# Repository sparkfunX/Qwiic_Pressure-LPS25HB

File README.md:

SparkFun Qwiic Pressure with LPS25HB
========================================

[*Qwiic Pressure Sensor - LPS25HB (SPX-14767)*](https://www.sparkfun.com/products/14767)

The LPS25HB is an absolute pressure sensor which means that it has an internal vacuum as a reference. (As opposed to *differential* and *gage* sensors, see [this](https://cdn.sparkfun.com/assets/e/1/2/4/1/HoneywellTechnicalNote_Absolute_v_Gage_pressure.pdf) description by Honeywell for more info) Absolute pressure sensors are often used as altimeters however they can be seen in other applications like the [Robotic Finger Sensor v2](https://www.sparkfun.com/products/14687). 

You can use this absolute pressure sensor to inform a drone autopilot of altitude, make a personal weather station, or maybe even help test someone's lung function! As part of the Qwiic system adding more capabilities like data logging with the [Qwiic OpenLog](https://www.sparkfun.com/products/14641) is a cinch!

The LPS25HB is the newest version of the LPS25H by STMicroelectronics featuring the widest range of sensing pressures (26 kPa to 126 kPa) and very high precision (as low as 1 Pa RMS, which equates to approximately 8 centimeters of air at sea level). Other features such as the 25 Hz update rate and durability to withstand nearly 2.5 MPa over-pressure make this a great choice for absolute pressure sensor. Additionally the LPS25HB comes in a stylish plastic IC package, as opposed to the standard metal casing seen on most other pressure sensors.

In addition to the Qwiic connectors this sensor breakout exposes the I2C and SPI lines as plated through hole (PTH) connections on either side. SPI access will allow for even faster communication with the sensor (up to 10 MHz!) 

This board is one of our many [Qwiic](https://www.sparkfun.com/qwiic) compatible boards! Simply plug and go. No soldering, no figuring out which is SDA or SCL, and no voltage regulation or translation required!

SparkFun labored with love to create this code. Feel like supporting open source hardware? 
Buy a [breakout board](https://www.sparkfun.com/products/14688) from SparkFun!

Repository Contents
-------------------

* **/Documents** - Datasheets
* **/Hardware** - Eagle design files (.brd, .sch)

Library
--------------
* **[Arduino Library](https://github.com/sparkfun/SparkFun_LPS25HB_Arduino_Library)** - Library for reading pressure and changing sensor settings

License Information
-------------------

This product is _**open source**_! 

If you have any questions or concerns on licensing, please contact techsupport@sparkfun.com.

Please use, reuse, and modify these files as you see fit. Please maintain attribution to SparkFun Electronics and release any derivative under the same license.

Distributed as-is; no warranty is given.

- Your friends at SparkFun.

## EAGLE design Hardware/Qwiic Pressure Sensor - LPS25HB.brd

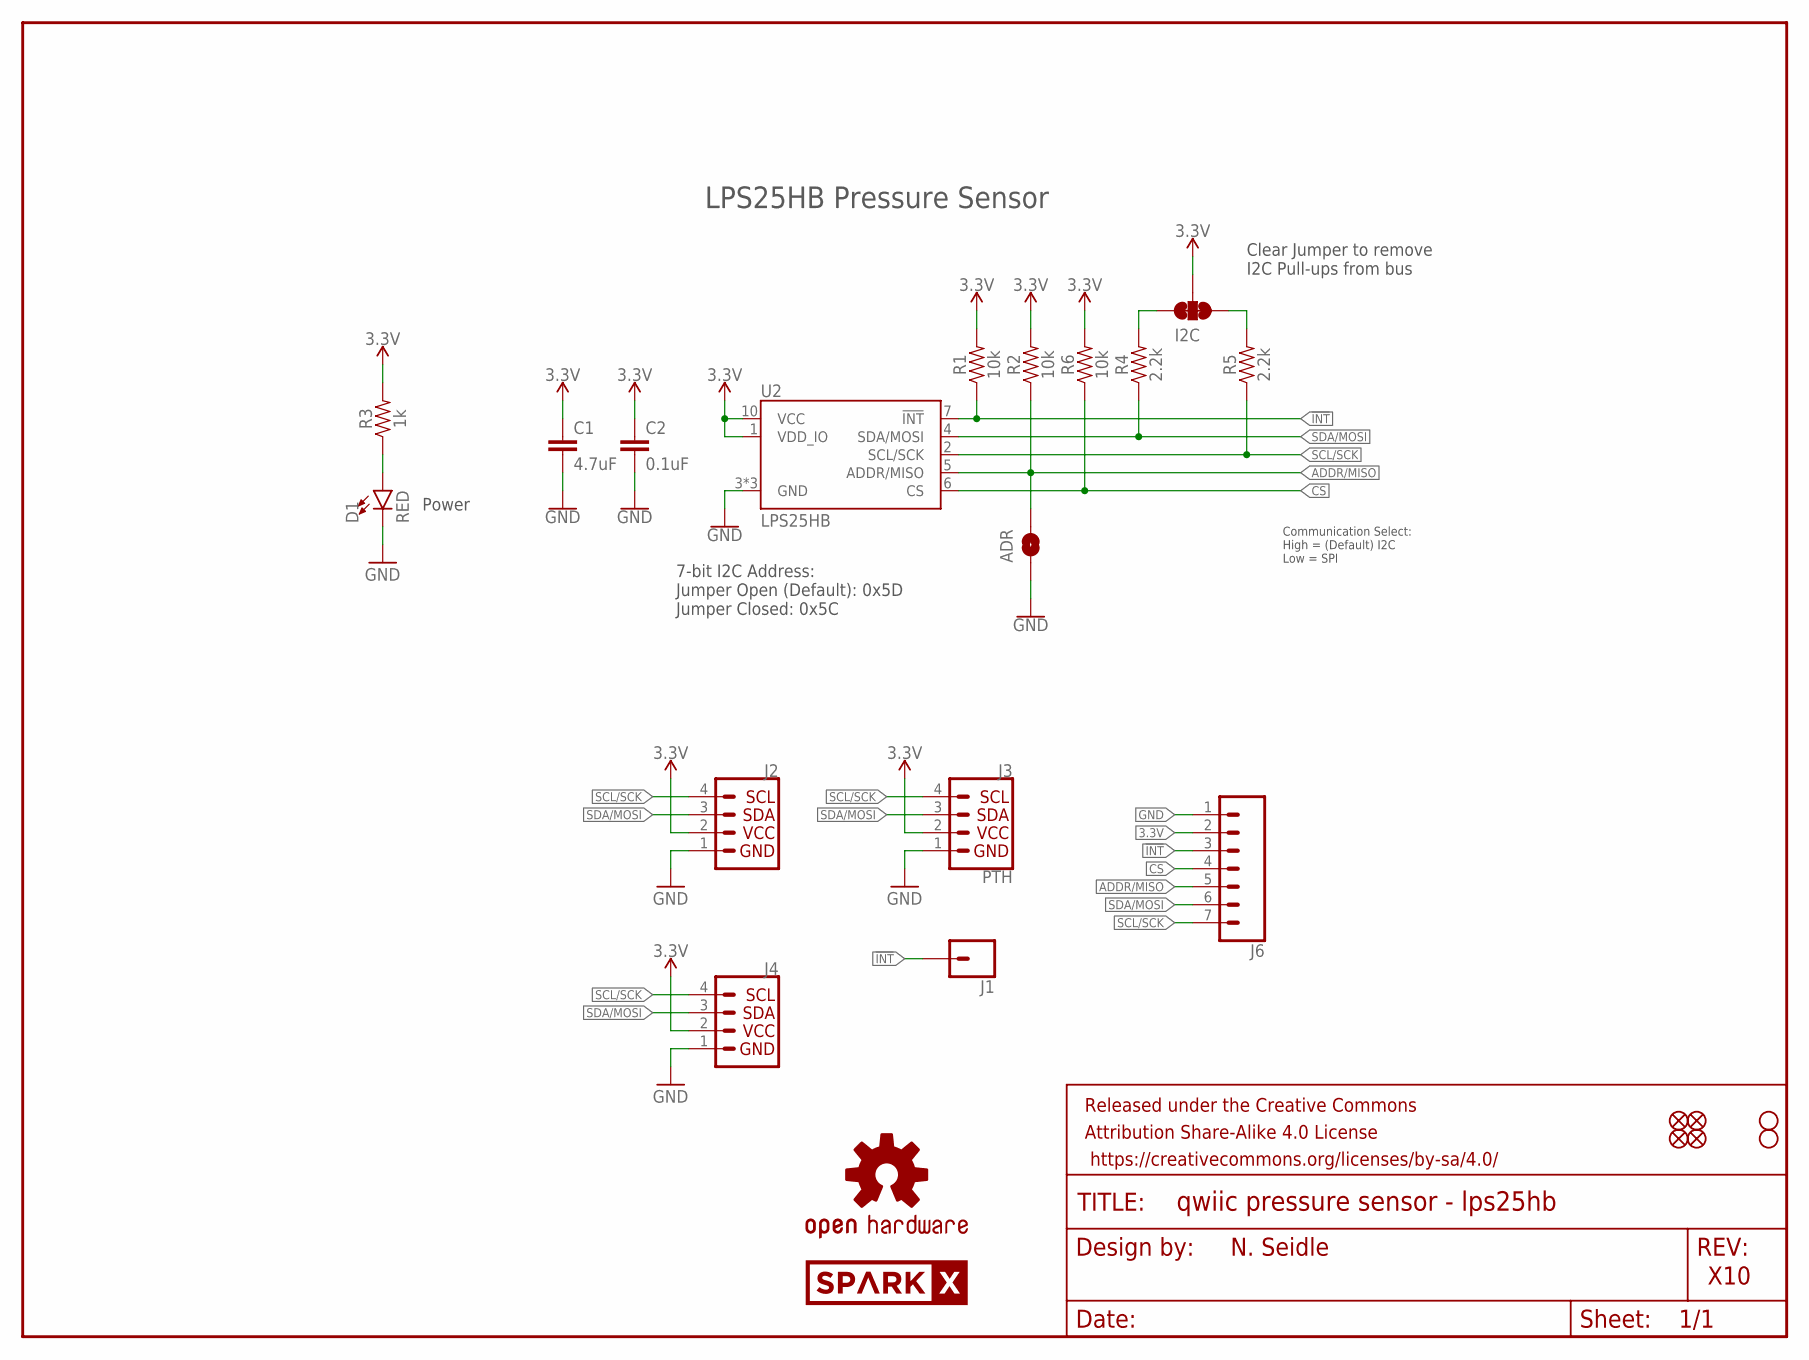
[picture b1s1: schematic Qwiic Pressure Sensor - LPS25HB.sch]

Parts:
ADR: JUMPER-SMT_2_NO_SILK; SMT-JUMPER_2_NO_SILK
C1: 4.7uF; 0603
C2: 0.1uF; 0603
D1: RED; LED-0603
FRAME1: FRAME-LETTER; CREATIVE_COMMONS
I2C: JUMPER-SMT_3_2-NC_TRACE_SILK; SMT-JUMPER_3_2-NC_TRACE_SILK
J1: CONN_01PTH_NO_SILK_YES_STOP; 1X01_NO_SILK
J2, J4: I2C_STANDARDQWIIC; 1X04_1MM_RA
J3: PTH; 1X04_NO_SILK
J6: CONN_07NO_SILK; 1X07_NO_SILK
JP1, JP2, JP5, JP6: FIDUCIALUFIDUCIAL; MICRO-FIDUCIAL
JP3, JP4: STAND-OFF
LOGO1: OSHW-LOGOMINI; OSHW-LOGO-MINI
R1, R2, R6: 10k; 0603
R3: 1k; 0603
R4, R5: 2.2k; 0603
U2: LPS25HB
U$2: SPARKX-LOGO4; SPARKX-MEDIUM

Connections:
3.3V: C1.1, C2.1, I2C.2, J2.2, J3.2 (VCC), J4.2, J6.2, R1.2, R2.2, R3.2, R6.2, U2.1 (VDD_IO), U2.10 (VCC)
!INT: J1.1, J6.3, R1.1, U2.7 (!INT)
ADDR/MISO: ADR.2, J6.5, R2.1, U2.5 (ADDR/MISO)
CS: J6.4, R6.1, U2.6 (CS)
GND: ADR.1, C1.2, C2.2, D1.C, J2.1, J3.1 (GND), J4.1, J6.1, U2.3 (GND), U2.8 (GND), U2.9 (GND)
unnamed: I2C.1, R5.2
unnamed: I2C.3, R4.2
unnamed: D1.A, R3.1
SCL/SCK: J2.4, J3.4 (SCL), J4.4, J6.7, R5.1, U2.2 (SCL/SCK)
SDA/MOSI: J2.3, J3.3 (SDA), J4.3, J6.6, R4.1, U2.4 (SDA/MOSI)

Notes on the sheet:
N. Seidle
X10
Clear Jumper to remove I2C Pull-ups from bus
Power
LPS25HB Pressure Sensor
7-bit I2C Address: Jumper Open (Default): 0x5D Jumper Closed: 0x5C
Communication Select: High = (Default) I2C Low = SPI

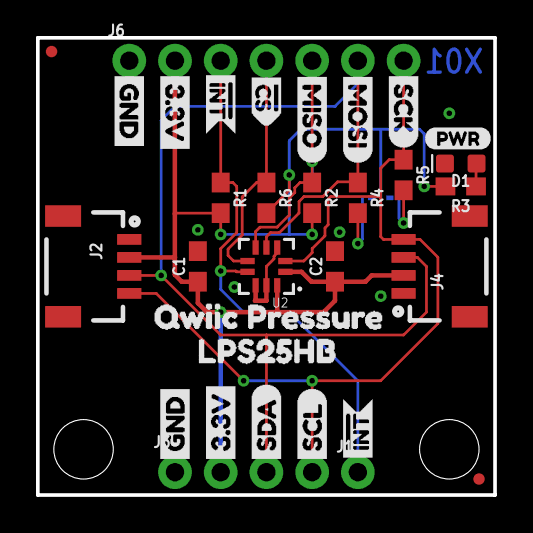
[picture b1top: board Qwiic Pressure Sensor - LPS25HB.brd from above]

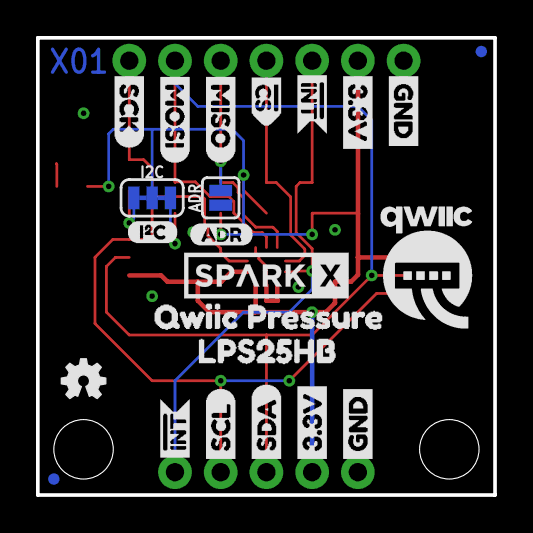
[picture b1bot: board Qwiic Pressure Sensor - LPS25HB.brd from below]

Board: 2 copper layers, 25.4 x 25.4 mm, 58 parts (23 on the bottom side), 10 nets.

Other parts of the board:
U$1, U$37: QWIIC_PRESSURE1
U$3, U$22, U$31, U$32: GND1
U$4, U$21, U$30, U$33: 3#3V2
U$5, U$27: SDA8
U$6, U$26: SCL9
U$7, U$35: LPS25HB0
U$9: QWIIC-LOGO-MEDIUM
U$10, U$11: MISO
U$12: I_SUPER2_C-()-03
U$15: PWR-()-03
U$16, U$17: MOSI
U$18, U$19: SCK-[)
U$20, U$23: CS#-[>
U$24, U$25, U$28, U$29: INT#-[<
U$34: ADR-()-03

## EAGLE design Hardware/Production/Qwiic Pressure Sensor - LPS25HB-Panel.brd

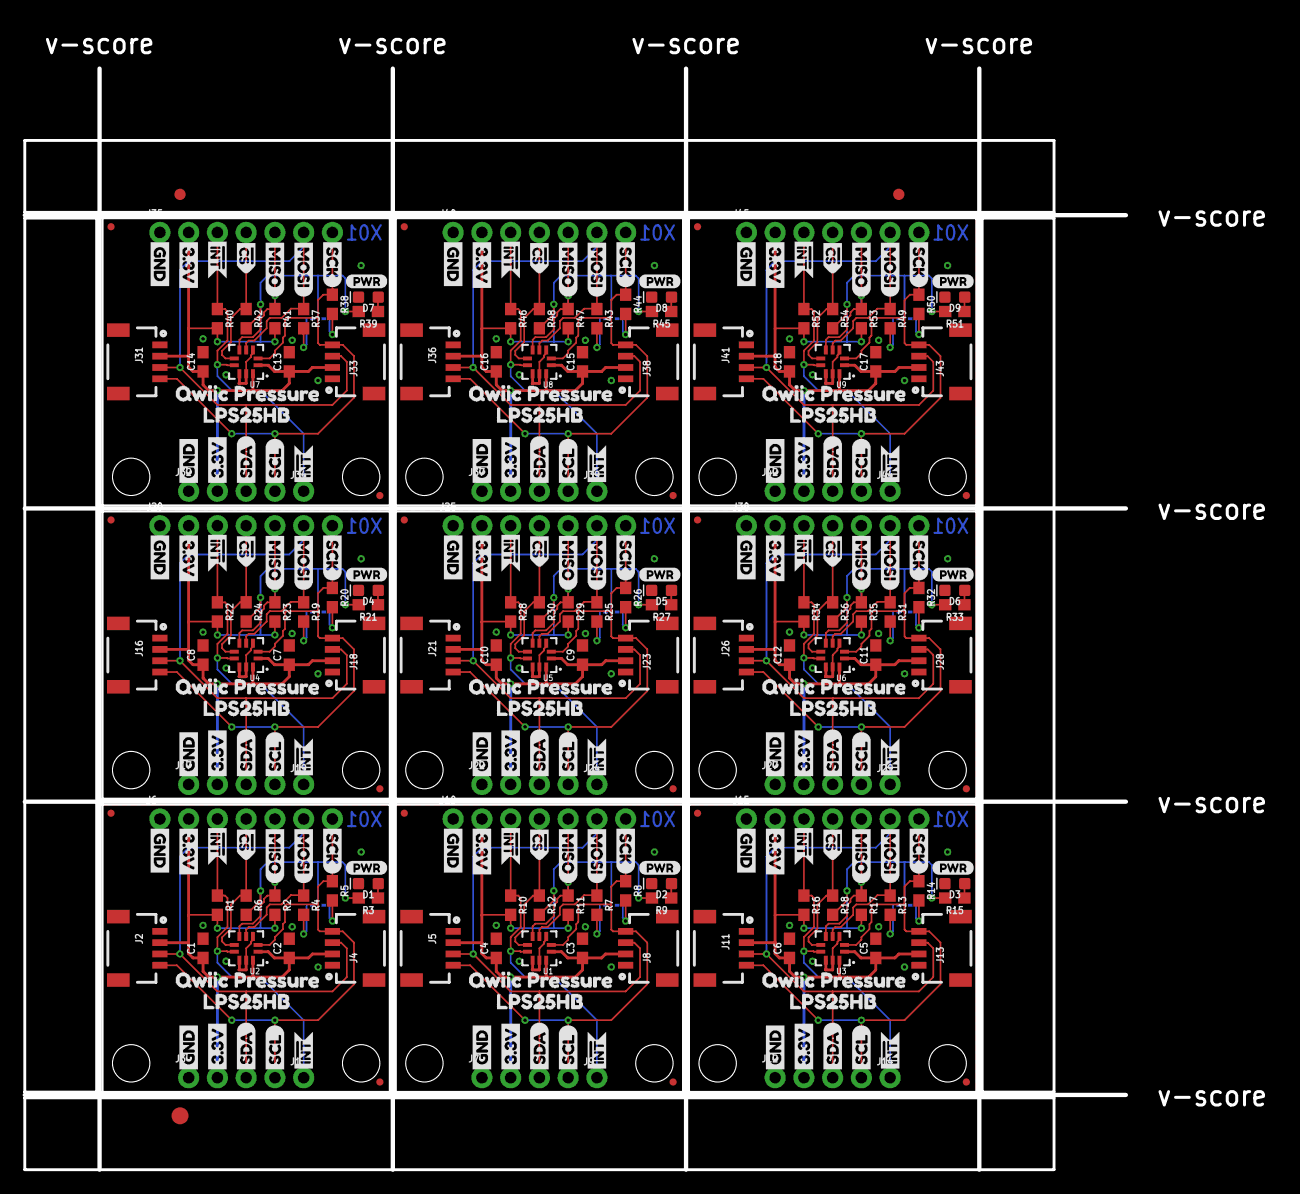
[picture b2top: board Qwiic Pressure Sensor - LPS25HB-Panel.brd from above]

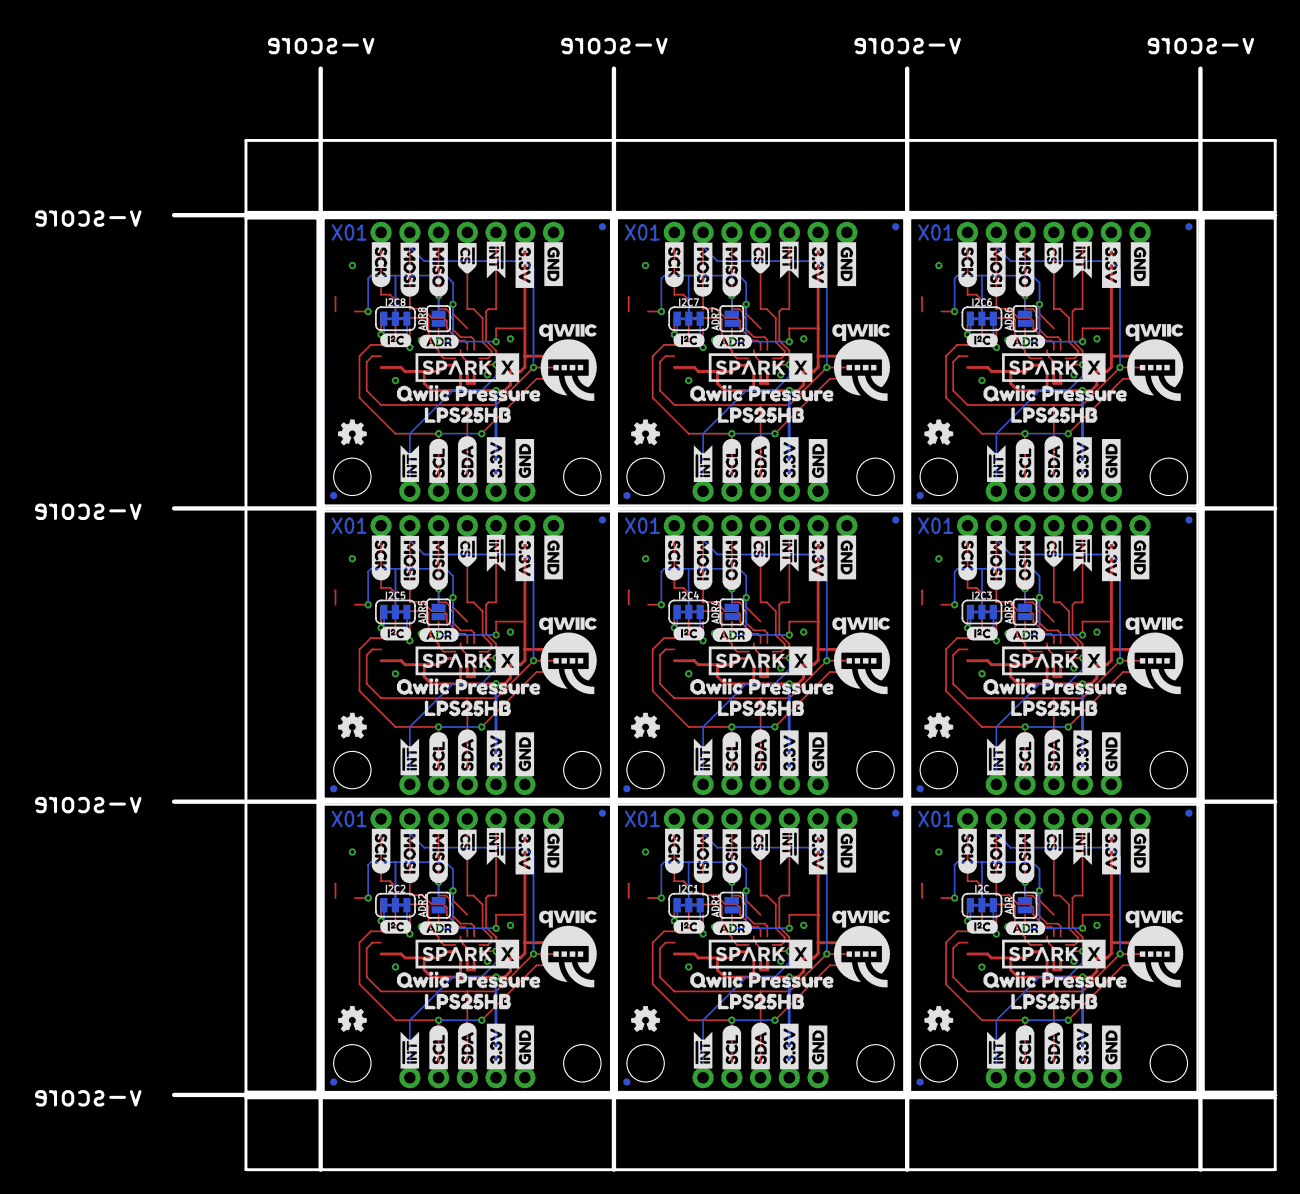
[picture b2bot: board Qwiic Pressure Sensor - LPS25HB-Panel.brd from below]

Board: 2 copper layers, 110.5 x 101.2 mm, 516 parts (207 on the bottom side), 90 nets.

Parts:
ADR, ADR1, ADR2, ADR3, ADR4, ADR5, ADR6, ADR7, ADR8: SMT-JUMPER_2_NO_SILK
C1, C4, C6, C8, C10, C12, C14, C16, C18: 4.7uF; 0603
C2, C3, C5, C7, C9, C11, C13, C15, C17: 0.1uF; 0603
D1, D2, D3, D4, D5, D6, D7, D8, D9: RED; LED-0603
E$1, E$2: FIDUCIAL-1X2
E$3: FIDUCIAL-1.5X3
I2C, I2C1, I2C2, I2C3, I2C4, I2C5, I2C6, I2C7, I2C8: SMT-JUMPER_3_2-NC_TRACE_SILK
J1, J9, J14, J19, J24, J29, J34, J39, J44: 1X01_NO_SILK
J2, J4, J5, J8, J11, J13, J16, J18, J21, J23, J26, J28, J31, J33, J36, J38, J41, J43: 1X04_1MM_RA
J3, J7, J12, J17, J22, J27, J32, J37, J42: PTH; 1X04_NO_SILK
J6, J10, J15, J20, J25, J30, J35, J40, J45: 1X07_NO_SILK
JP1, JP2, JP5, JP6, JP9, JP10, JP11, JP12, JP15, JP16, JP17, JP18, JP21, JP22, JP23, JP24, JP27, JP28, JP29, JP30, JP33, JP34, JP35, JP36, JP39, JP40, JP41, JP42, JP45, JP46, JP47, JP48, JP51, JP52, JP53, JP54: FIDUCIALUFIDUCIAL; MICRO-FIDUCIAL
JP3, JP4, JP7, JP8, JP13, JP14, JP19, JP20, JP25, JP26, JP31, JP32, JP37, JP38, JP43, JP44, JP49, JP50: STAND-OFF
LOGO1, LOGO2, LOGO3, LOGO4, LOGO5, LOGO6, LOGO7, LOGO8, LOGO9: OSHW-LOGOMINI; OSHW-LOGO-MINI
R1, R2, R6, R10, R11, R12, R16, R17, R18, R22, R23, R24, R28, R29, R30, R34, R35, R36, R40, R41, R42, R46, R47, R48, R52, R53, R54: 10k; 0603
R3, R9, R15, R21, R27, R33, R39, R45, R51: 1k; 0603
R4, R5, R7, R8, R13, R14, R19, R20, R25, R26, R31, R32, R37, R38, R43, R44, R49, R50: 2.2k; 0603
U1, U2, U3, U4, U5, U6, U7, U8, U9: LPS25HB
U$1, U$37, U$64, U$65, U$97, U$98, U$130, U$131, U$163, U$164, U$196, U$197, U$229, U$230, U$262, U$263, U$295, U$296: QWIIC_PRESSURE1
U$2, U$8, U$67, U$100, U$133, U$166, U$199, U$232, U$265: SPARKX-LOGO4; SPARKX-MEDIUM
U$3, U$14, U$22, U$31, U$32, U$39, U$59, U$60, U$69, U$72, U$92, U$93, U$102, U$105, U$125, U$126, U$135, U$138, U$158, U$159, U$168, U$171, U$191, U$192, U$201, U$204, U$224, U$225, U$234, U$237, U$257, U$258, U$267, U$270, U$290, U$291: GND1
U$4, U$13, U$21, U$30, U$33, U$40, U$58, U$61, U$68, U$73, U$91, U$94, U$101, U$106, U$124, U$127, U$134, U$139, U$157, U$160, U$167, U$172, U$190, U$193, U$200, U$205, U$223, U$226, U$233, U$238, U$256, U$259, U$266, U$271, U$289, U$292: 3#3V2
U$5, U$27, U$38, U$41, U$71, U$74, U$104, U$107, U$137, U$140, U$170, U$173, U$203, U$206, U$236, U$239, U$269, U$272: SDA8
U$6, U$26, U$36, U$42, U$70, U$75, U$103, U$108, U$136, U$141, U$169, U$174, U$202, U$207, U$235, U$240, U$268, U$273: SCL9
U$7, U$35, U$63, U$66, U$96, U$99, U$129, U$132, U$162, U$165, U$195, U$198, U$228, U$231, U$261, U$264, U$294, U$297: LPS25HB0
U$9, U$43, U$76, U$109, U$142, U$175, U$208, U$241, U$274: QWIIC-LOGO-MEDIUM
U$10, U$11, U$46, U$47, U$79, U$80, U$112, U$113, U$145, U$146, U$178, U$179, U$211, U$212, U$244, U$245, U$277, U$278: MISO
U$12, U$44, U$77, U$110, U$143, U$176, U$209, U$242, U$275: I_SUPER2_C-()-03
U$15, U$45, U$78, U$111, U$144, U$177, U$210, U$243, U$276: PWR-()-03
U$16, U$17, U$48, U$49, U$81, U$82, U$114, U$115, U$147, U$148, U$180, U$181, U$213, U$214, U$246, U$247, U$279, U$280: MOSI
U$18, U$19, U$50, U$51, U$83, U$84, U$116, U$117, U$149, U$150, U$182, U$183, U$215, U$216, U$248, U$249, U$281, U$282: SCK-[)
U$20, U$23, U$52, U$53, U$85, U$86, U$118, U$119, U$151, U$152, U$184, U$185, U$217, U$218, U$250, U$251, U$283, U$284: CS#-[>
U$24, U$25, U$28, U$29, U$54, U$55, U$56, U$57, U$87, U$88, U$89, U$90, U$120, U$121, U$122, U$123, U$153, U$154, U$155, U$156, U$186, U$187, U$188, U$189, U$219, U$220, U$221, U$222, U$252, U$253, U$254, U$255, U$285, U$286, U$287, U$288: INT#-[<
U$34, U$62, U$95, U$128, U$161, U$194, U$227, U$260, U$293: ADR-()-03

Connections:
3.3V: C1.1, C2.1, I2C.2, J2.2, J3.2, J4.2, J6.2, R1.2, R2.2, R3.2, R6.2, U2.1, U2.10
3.3V1: C3.1, C4.1, I2C1.2, J5.2, J7.2, J8.2, J10.2, R9.2, R10.2, R11.2, R12.2, U1.1, U1.10
3.3V2: C5.1, C6.1, I2C2.2, J11.2, J12.2, J13.2, J15.2, R15.2, R16.2, R17.2, R18.2, U3.1, U3.10
3.3V3: C7.1, C8.1, I2C3.2, J16.2, J17.2, J18.2, J20.2, R21.2, R22.2, R23.2, R24.2, U4.1, U4.10
3.3V4: C9.1, C10.1, I2C4.2, J21.2, J22.2, J23.2, J25.2, R27.2, R28.2, R29.2, R30.2, U5.1, U5.10
3.3V5: C11.1, C12.1, I2C5.2, J26.2, J27.2, J28.2, J30.2, R33.2, R34.2, R35.2, R36.2, U6.1, U6.10
3.3V6: C13.1, C14.1, I2C6.2, J31.2, J32.2, J33.2, J35.2, R39.2, R40.2, R41.2, R42.2, U7.1, U7.10
3.3V7: C15.1, C16.1, I2C7.2, J36.2, J37.2, J38.2, J40.2, R45.2, R46.2, R47.2, R48.2, U8.1, U8.10
3.3V8: C17.1, C18.1, I2C8.2, J41.2, J42.2, J43.2, J45.2, R51.2, R52.2, R53.2, R54.2, U9.1, U9.10
!INT: J1.1, J6.3, R1.1, U2.7
!INT1: J9.1, J10.3, R10.1, U1.7
!INT2: J14.1, J15.3, R16.1, U3.7
!INT3: J19.1, J20.3, R22.1, U4.7
!INT4: J24.1, J25.3, R28.1, U5.7
!INT5: J29.1, J30.3, R34.1, U6.7
!INT6: J34.1, J35.3, R40.1, U7.7
!INT7: J39.1, J40.3, R46.1, U8.7
!INT8: J44.1, J45.3, R52.1, U9.7
ADDR/MISO: ADR.2, J6.5, R2.1, U2.5
ADDR/MISO1: ADR1.2, J10.5, R11.1, U1.5
ADDR/MISO2: ADR2.2, J15.5, R17.1, U3.5
ADDR/MISO3: ADR3.2, J20.5, R23.1, U4.5
ADDR/MISO4: ADR4.2, J25.5, R29.1, U5.5
ADDR/MISO5: ADR5.2, J30.5, R35.1, U6.5
ADDR/MISO6: ADR6.2, J35.5, R41.1, U7.5
ADDR/MISO7: ADR7.2, J40.5, R47.1, U8.5
ADDR/MISO8: ADR8.2, J45.5, R53.1, U9.5
CS: J6.4, R6.1, U2.6
CS1: J10.4, R12.1, U1.6
CS2: J15.4, R18.1, U3.6
CS3: J20.4, R24.1, U4.6
CS4: J25.4, R30.1, U5.6
CS5: J30.4, R36.1, U6.6
CS6: J35.4, R42.1, U7.6
CS7: J40.4, R48.1, U8.6
CS8: J45.4, R54.1, U9.6
GND: ADR.1, C1.2, C2.2, D1.C, J2.1, J3.1, J4.1, J6.1, U2.3, U2.8, U2.9
GND1: ADR1.1, C3.2, C4.2, D2.C, J5.1, J7.1, J8.1, J10.1, U1.3, U1.8, U1.9
GND2: ADR2.1, C5.2, C6.2, D3.C, J11.1, J12.1, J13.1, J15.1, U3.3, U3.8, U3.9
GND3: ADR3.1, C7.2, C8.2, D4.C, J16.1, J17.1, J18.1, J20.1, U4.3, U4.8, U4.9
GND4: ADR4.1, C9.2, C10.2, D5.C, J21.1, J22.1, J23.1, J25.1, U5.3, U5.8, U5.9
GND5: ADR5.1, C11.2, C12.2, D6.C, J26.1, J27.1, J28.1, J30.1, U6.3, U6.8, U6.9
GND6: ADR6.1, C13.2, C14.2, D7.C, J31.1, J32.1, J33.1, J35.1, U7.3, U7.8, U7.9
GND7: ADR7.1, C15.2, C16.2, D8.C, J36.1, J37.1, J38.1, J40.1, U8.3, U8.8, U8.9
GND8: ADR8.1, C17.2, C18.2, D9.C, J41.1, J42.1, J43.1, J45.1, U9.3, U9.8, U9.9
unnamed: I2C.1, R5.2
unnamed: I2C.3, R4.2
unnamed: D1.A, R3.1
unnamed: I2C1.1, R8.2
unnamed: I2C1.3, R7.2
unnamed: D2.A, R9.1
unnamed: I2C2.1, R14.2
unnamed: I2C2.3, R13.2
unnamed: D3.A, R15.1
unnamed: I2C3.1, R20.2
unnamed: I2C3.3, R19.2
unnamed: D4.A, R21.1
unnamed: I2C4.1, R26.2
unnamed: I2C4.3, R25.2
unnamed: D5.A, R27.1
unnamed: I2C5.1, R32.2
unnamed: I2C5.3, R31.2
unnamed: D6.A, R33.1
unnamed: I2C6.1, R38.2
unnamed: I2C6.3, R37.2
unnamed: D7.A, R39.1
unnamed: I2C7.1, R44.2
unnamed: I2C7.3, R43.2
unnamed: D8.A, R45.1
unnamed: I2C8.1, R50.2
unnamed: I2C8.3, R49.2
unnamed: D9.A, R51.1
SCL/SCK: J2.4, J3.4, J4.4, J6.7, R5.1, U2.2
SCL/SCK1: J5.4, J7.4, J8.4, J10.7, R8.1, U1.2
SCL/SCK2: J11.4, J12.4, J13.4, J15.7, R14.1, U3.2
SCL/SCK3: J16.4, J17.4, J18.4, J20.7, R20.1, U4.2
SCL/SCK4: J21.4, J22.4, J23.4, J25.7, R26.1, U5.2
SCL/SCK5: J26.4, J27.4, J28.4, J30.7, R32.1, U6.2
SCL/SCK6: J31.4, J32.4, J33.4, J35.7, R38.1, U7.2
SCL/SCK7: J36.4, J37.4, J38.4, J40.7, R44.1, U8.2
SCL/SCK8: J41.4, J42.4, J43.4, J45.7, R50.1, U9.2
SDA/MOSI: J2.3, J3.3, J4.3, J6.6, R4.1, U2.4
SDA/MOSI1: J5.3, J7.3, J8.3, J10.6, R7.1, U1.4
SDA/MOSI2: J11.3, J12.3, J13.3, J15.6, R13.1, U3.4
SDA/MOSI3: J16.3, J17.3, J18.3, J20.6, R19.1, U4.4
SDA/MOSI4: J21.3, J22.3, J23.3, J25.6, R25.1, U5.4
SDA/MOSI5: J26.3, J27.3, J28.3, J30.6, R31.1, U6.4
SDA/MOSI6: J31.3, J32.3, J33.3, J35.6, R37.1, U7.4
SDA/MOSI7: J36.3, J37.3, J38.3, J40.6, R43.1, U8.4
SDA/MOSI8: J41.3, J42.3, J43.3, J45.6, R49.1, U9.4

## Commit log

2018-05-30 Created library files
2018-05-30 Added register definitions and configurations
2018-05-31 Demonstrated working library
    One possible issue: the value in the temperature registers appears to be wrong. Verified that the correct registers were accessed by scoping the data lines, and also saw that the returned value was u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
2018-05-31 Small updates
2018-06-01 Organized files
2020-02-13 Add test sketch

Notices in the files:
parts and their libraries:
SparkFun-Resistors: Licensing: Creative Commons ShareAlike 4.0 International - https://creativecommons.org/licenses/by-sa/4.0
SparkFun-Aesthetics: Released under the Creative Commons Attribution Share-Alike 4.0 License
SparkFun-Aesthetics: https://creativecommons.org/licenses/by-sa/4.0
